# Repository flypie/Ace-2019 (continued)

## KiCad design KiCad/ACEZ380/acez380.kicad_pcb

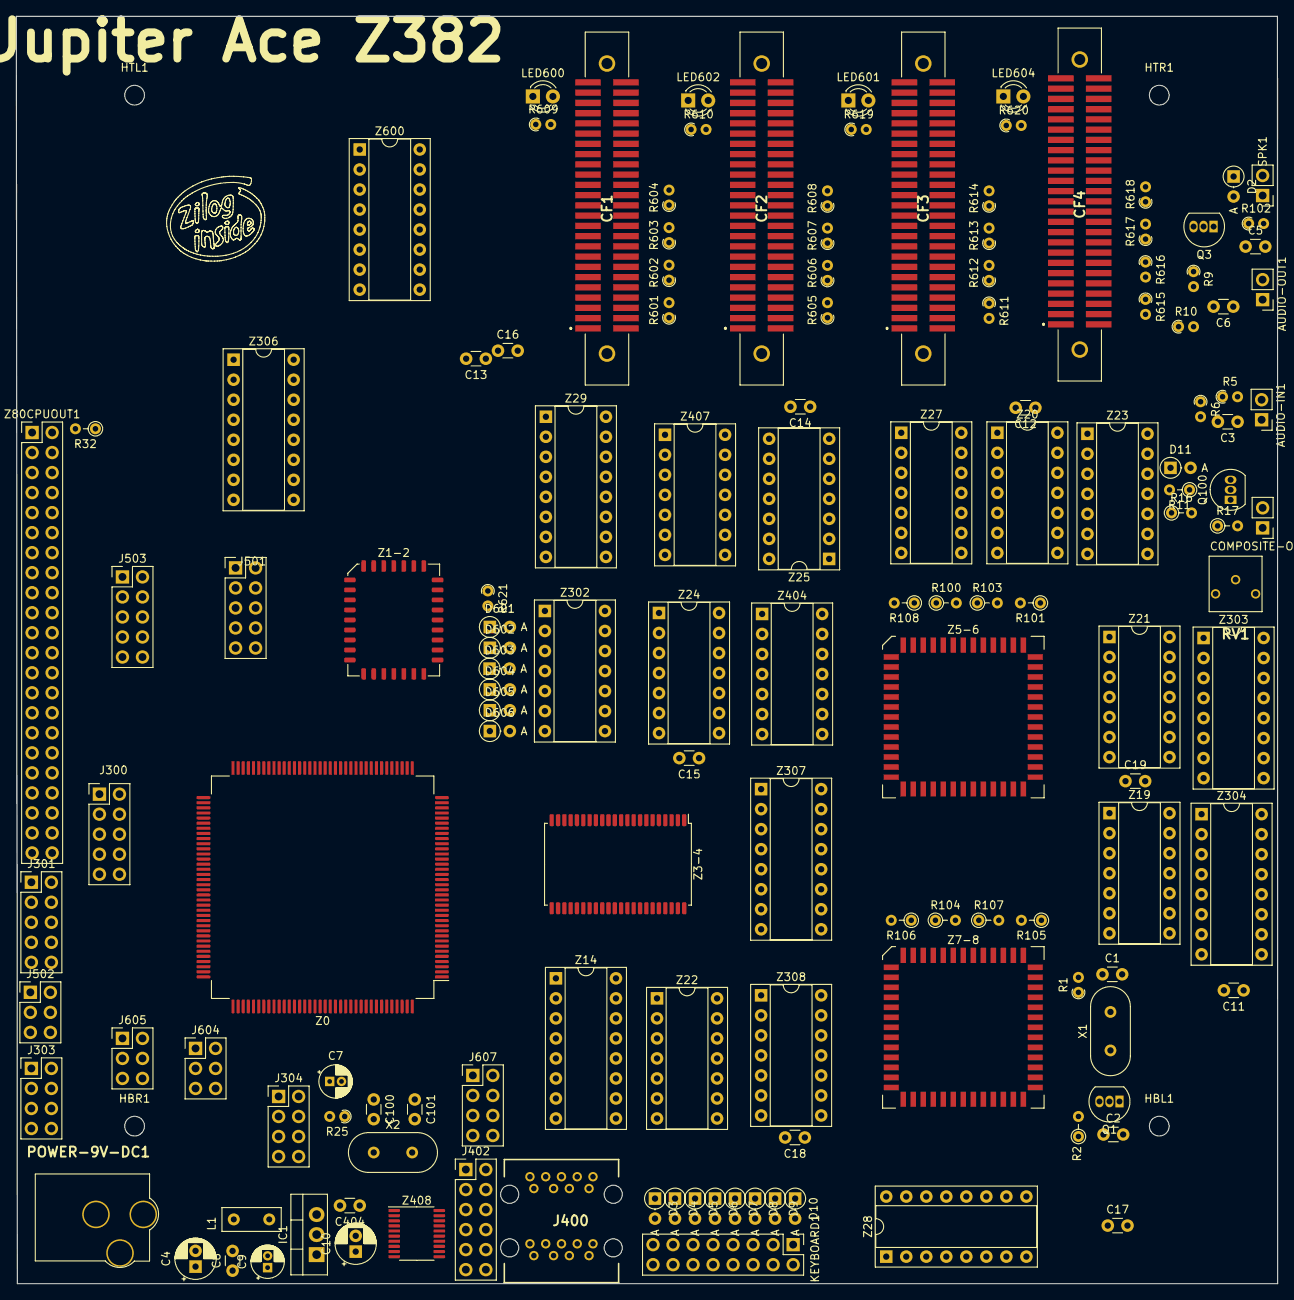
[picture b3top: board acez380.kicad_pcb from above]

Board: 2 copper layers, 160.0 x 160.8 mm, 146 parts (0 on the bottom side), 266 nets, no tracks yet.

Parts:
AUDIO-IN1: 332-02; PinHeader_1x02_P2.54mm_Vertical
AUDIO-OUT1: 332-02; PinHeader_1x02_P2.54mm_Vertical
C1: 30p; C_Disc_D3.0mm_W1.6mm_P2.50mm
C2: 100p; C_Disc_D3.0mm_W1.6mm_P2.50mm
C3, C6: 47nF; C_Disc_D3.0mm_W1.6mm_P2.50mm
C4, C10: 100uf; CP_Radial_D5.0mm_P2.00mm
C5: 47pF; C_Disc_D3.0mm_W1.6mm_P2.50mm
C7: 1U; CP_Radial_D4.0mm_P1.50mm
C8, C11, C12, C13, C14, C15, C16, C17, C18, C19: 100nf; C_Disc_D3.0mm_W1.6mm_P2.50mm
C9: 100uf; CP_Radial_D4.0mm_P1.50mm
C100, C101: 22p; C_Disc_D3.0mm_W1.6mm_P2.50mm
C404: 1u; C_Disc_D3.0mm_W1.6mm_P2.50mm
CF1, CF2, CF3, CF4: 5788643-1; 57886431
COMPOSITE-OUT1: COMPOSITE-OUT1; PinHeader_1x02_P2.54mm_Vertical
D2, D3, D4, D5, D6, D7, D8, D9, D10, D11, D601, D602, D603, D604, D605, D606: 1N4148; D_DO-35_SOD27_P2.54mm_Vertical_AnodeUp
HBL1: MountingHole; MountingHole_2.5mm
HBR1: MountingHole; MountingHole_2.5mm
HTL1: MountingHole; MountingHole_2.5mm
HTR1: MountingHole; MountingHole_2.5mm
IC1: LM7805_TO220; TO-220-3_Vertical
J300, J301, J501, J503: Conn_02x05_Odd_Even; PinHeader_2x05_P2.54mm_Vertical
J303, J304, J607: Conn_02x04_Odd_Even; PinHeader_2x04_P2.54mm_Vertical
J400: 48409-0003
J402: Conn_02x06_Odd_Even; PinHeader_2x06_P2.54mm_Vertical
J502, J604, J605: Conn_02x03_Odd_Even; PinHeader_2x03_P2.54mm_Vertical
KEYBOARD1: Conn_02x08_Odd_Even; PinHeader_2x08_P2.54mm_Vertical
L1: 100 nH; KEMET_SBT_0260T
LED600, LED601, LED602, LED604: WP3A8HD; LED_D3.0mm
Logo1: ZilogBack; ZilogInsideBack
Logo2: ZilogFront; ZilogInsideFront
POWER-9V-DC1: Conn_01x02; 163179PHEX
Q1, Q100: 2N3904; TO-92_Inline
Q3: BC183; TO-92L_Inline
R1: 4k7; R_Axial_DIN0204_L3.6mm_D1.6mm_P1.90mm_Vertical
R2: 47k; R_Axial_DIN0204_L3.6mm_D1.6mm_P2.54mm_Vertical
R5, R601, R602, R603, R604, R605, R606, R607, R608, R611, R612, R613, R614, R615, R616, R617, R618: 1K; R_Axial_DIN0204_L3.6mm_D1.6mm_P1.90mm_Vertical
R6: 12k; R_Axial_DIN0204_L3.6mm_D1.6mm_P1.90mm_Vertical
R9: 22k; R_Axial_DIN0204_L3.6mm_D1.6mm_P1.90mm_Vertical
R10: 10k; R_Axial_DIN0204_L3.6mm_D1.6mm_P1.90mm_Vertical
R11, R16: 1K5; R_Axial_DIN0204_L3.6mm_D1.6mm_P2.54mm_Vertical
R17: 100; R_Axial_DIN0204_L3.6mm_D1.6mm_P2.54mm_Vertical
R25: 220k; R_Axial_DIN0204_L3.6mm_D1.6mm_P1.90mm_Vertical
R32: 1K0; R_Axial_DIN0204_L3.6mm_D1.6mm_P2.54mm_Vertical
R100, R101, R103, R104, R105, R106, R107, R108: 270; R_Axial_DIN0204_L3.6mm_D1.6mm_P2.54mm_Vertical
R102: 200; R_Axial_DIN0204_L3.6mm_D1.6mm_P1.90mm_Vertical
R609, R610, R619, R620: 500; R_Axial_DIN0204_L3.6mm_D1.6mm_P1.90mm_Vertical
R621: 10; R_Axial_DIN0204_L3.6mm_D1.6mm_P1.90mm_Vertical
RV1: 100; 3362H1103LF
SPK1: SPk1; PinHeader_1x02_P2.54mm_Vertical
X1: CRYSTALHC49U-V 6.556MHz; Crystal_HC49-U_Vertical
X2: 20MHz; Crystal_HC49-U_Vertical
Z0: Z80-182-L182-VQFP-100; PQFP-144_28x28mm_P0.65mm
Z1-2: SST39SF010-LCC; PLCC-32_11.4x14.0mm_P1.27mm
Z3-4: CY62158; TSOP-II-44_10.16x18.41mm_P0.8mm
Z5-6: IDT71321-421-52PIN-PLCC; PLCC-52
Z7-8: IDT71321; PLCC-52
Z14: SN74LS367AN; DIP-16_W7.62mm_Socket
Z19: 74AHCT00; DIP-14_W7.62mm_Socket
Z20: 74AHCT08; DIP-14_W7.62mm_Socket
Z21, Z22: 74AHCT11; DIP-14_W7.62mm_Socket
Z23: 74AHCT86; DIP-14_W7.62mm_Socket
Z24: SN74AHCT02N; DIP-14_W7.62mm_Socket
Z25: 74AHCT02; DIP-14_W7.62mm_Socket
Z27: SN74AHCT74N; DIP-14_W7.62mm_Socket
Z28: 74AHCT166; DIP-16_W7.62mm_Socket
Z29: SN74AHCT138N; DIP-16_W7.62mm_Socket
Z80CPUOUT1: Conn_02x22_Odd_Even; PinHeader_2x22_P2.54mm_Vertical
Z302: 74AHCT32; DIP-14_W7.62mm_Socket
Z303, Z304: CD74HCT4040E; DIP-16_W7.62mm_Socket
Z306: SN74AHCT04N; DIP-16_W7.62mm_Socket
Z307, Z600: SN74AHCT139N; DIP-16_W7.62mm_Socket
Z308: SN74AHCT04N; DIP-14_W7.62mm_Socket
Z404: 74LS21; DIP-14_W7.62mm_Socket
Z407: 74AHCT30D; DIP-14_W7.62mm_Socket
Z408: STM8S003F3P; TSSOP-20_4.4x6.5mm_P0.65mm

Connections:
50Hz: Z21.6, Z25.6, Z306.9
+5V: C10.1, C11.1, C12.1, C13.1, C14.1, C15.1, C16.1, C17.1, C18.1, C19.1, CF1.13 (Vcc), CF1.38 (Vcc), CF2.13 (Vcc), CF2.38 (Vcc), CF3.13 (Vcc), CF3.38 (Vcc), CF4.13 (Vcc), CF4.38 (Vcc), D2.1 (K), IC1.3 (VO), J300.9, J301.9, J303.7, J304.7, J400.1, J400.10, J402.11, J501.9, J502.5, J503.9, J604.5, J605.5, J607.7, Q100.3 (C), R1.1, R16.2, R25.1, R100.1, R101.1, R103.1, R104.1, R105.1, R106.1, R107.1, R108.1, R601.1, R602.1, R603.1, R604.1, R605.1, R606.1, R607.1, R608.1, R609.1, R610.1, R611.1, R612.1, R613.1, R614.1, R615.1, R616.1, R617.1, R618.1, R619.1, R620.1, SPK1.2, Z0.5 (VDD_1), Z0.23 (VDD_2), Z0.41 (VDD_3), Z0.59 (VDD_4), Z0.77 (VDD_5), Z0.86 (VSS_6), Z0.95 (VDD_6), Z0.113 (VDD_7), Z0.131 (VDD_8), Z1-2.32 (VCC), Z3-4.11 (VCC1), Z3-4.33 (VCC2), Z3-4.40 (CE2), Z5-6.51 (~CER), Z5-6.52 (VCC), Z7-8.51 (~CER), Z7-8.52 (VCC), Z14.16 (VCC), Z19.14 (VCC), Z20.14 (VCC), Z21.14 (VCC), Z22.14 (VCC), Z23.14 (VCC), Z24.14 (VCC), Z25.14 (VCC), Z27.1 (~R), Z27.4 (~S), Z27.10 (~S), Z27.13 (~R), Z27.14 (VCC), Z28.9 (Clr), Z28.16 (VCC), Z29.16 (VCC), Z80CPUOUT1.37, Z302.14 (VCC), Z303.16 (VDD), Z304.16 (VDD), Z306.14 (VCC), Z307.16 (VCC), Z308.14 (VCC), Z404.14 (VCC), Z407.14 (VCC), Z408.9 (VDD), Z600.16 (VCC)
+9V: C4.1, C8.1, L1.1, POWER-9V-DC1.A
+9Vsm: C9.1, IC1.1 (VI), L1.2, Z80CPUOUT1.39
/ADDRDECODE/~3C00-3FFF: Z302.6, Z407.11, Z407.12
/ADDRDECODE/~CPUFONT: Z302.9, Z302.12, Z307.5 (O1)
/VDG/INVERTCHAR: Z5-6.34 (I/O7R), Z20.13
/VDG/SH~LD: Z5-6.46 (~OER), Z5-6.50 (R~WR), Z7-8.46 (~OER), Z7-8.50 (R~WR), Z19.6, Z28.15 (PE)
/VDG/VIDEN: Z19.4, Z20.9, Z22.6
/VDG/VIDEO: D11.2 (A), Q100.2 (B), R11.1, R16.1
/~BUSAK: Z0.132 (~BUSACK), Z80CPUOUT1.28
/~BUSRQ: Z0.133 (~BUSREQ), Z80CPUOUT1.24
/~HALT: Z0.121 (~HALT), Z80CPUOUT1.38
/~WAIT: Z0.130 (~WAIT), Z80CPUOUT1.26
/~WE: R32.2, Z80CPUOUT1.1
A0: Z0.22 (A0), Z1-2.12 (A0), Z3-4.5 (A0), Z5-6.7 (A0L), Z7-8.7 (A0L), Z80CPUOUT1.7, Z307.14 (A0)
A1: Z0.21 (A1), Z1-2.11 (A1), Z3-4.4 (A1), Z5-6.8 (A1L), Z7-8.8 (A1L), Z80CPUOUT1.8, Z307.13 (A1)
A2: Z0.20 (A2), Z1-2.10 (A2), Z3-4.3 (A2), Z5-6.9 (A2L), Z7-8.9 (A2L), Z80CPUOUT1.17, Z308.3
A3: Z0.19 (A3), Z1-2.9 (A3), Z3-4.2 (A3), Z5-6.10 (A3L), Z7-8.10 (A3L), Z80CPUOUT1.10, Z308.4
A4: Z0.18 (A4), Z1-2.8 (A4), Z3-4.1 (A4), Z5-6.11 (A4L), Z7-8.11 (A4L), Z80CPUOUT1.12, Z308.5
A5: Z0.17 (A5), Z1-2.7 (A5), Z3-4.44 (A5), Z5-6.12 (A5L), Z7-8.12 (A5L), Z80CPUOUT1.14, Z308.6
A6: Z0.16 (A6), Z1-2.6 (A6), Z3-4.43 (A6), Z5-6.13 (A6L), Z7-8.13 (A6L), Z80CPUOUT1.16, Z308.11
A7: Z0.15 (A7), Z1-2.5 (A7), Z3-4.42 (A7), Z5-6.14 (A7L), Z7-8.14 (A7L), Z80CPUOUT1.9, Z308.12
A8: D10.1 (K), Z0.13 (A8), Z1-2.27 (A8), Z3-4.39 (A8), Z5-6.15 (A8L), Z7-8.15 (A8L), Z80CPUOUT1.11, Z600.3 (A1)
A9: D9.1 (K), Z0.12 (A9), Z1-2.26 (A9), Z3-4.28 (A9), Z5-6.16 (A9L), Z7-8.16 (A9L), Z80CPUOUT1.13, Z600.2 (A0)
A10: CF1.18 (A2), CF2.18 (A2), CF3.18 (A2), CF4.18 (A2), D8.1 (K), Z0.11 (A10), Z1-2.23 (A10), Z3-4.27 (A10), Z80CPUOUT1.15, Z302.2, Z306.11
A11: CF1.19 (A1), CF2.19 (A1), CF3.19 (A1), CF4.19 (A1), D7.1 (K), Z0.10 (A11), Z1-2.25 (A11), Z3-4.26 (A11), Z80CPUOUT1.33, Z307.2 (A0)
A12: CF1.20 (A0), CF2.20 (A0), CF3.20 (A0), CF4.20 (A0), D6.1 (K), Z0.9 (A12), Z1-2.4 (A12), Z3-4.25 (A12), Z80CPUOUT1.31, Z307.3 (A1)
A13: D5.1 (K), Z0.8 (A13), Z1-2.28 (A13), Z3-4.24 (A13), Z29.1 (A0), Z80CPUOUT1.29
A14: D4.1 (K), D606.2 (A), Z0.7 (A14), Z1-2.29 (A14), Z3-4.23 (A14), Z29.2 (A1), Z80CPUOUT1.27
A15: D3.1 (K), D605.2 (A), Z0.6 (A15), Z1-2.2 (A16), Z3-4.22 (A15), Z29.3 (A2), Z80CPUOUT1.25
A16: D604.2 (A), Z0.4 (A16), Z1-2.3 (A15), Z3-4.21 (A16)
A17: D603.2 (A), Z0.3 (A17), Z3-4.20 (A17)
A18: D602.2 (A), Z0.2 (A18), Z3-4.19 (A18)
A19: D601.2 (A), Z0.1 (A19), Z3-4.18 (A19)
A20: J607.1, Z0.144 (A20)
A21: J607.3, Z0.143 (A21)
A22: J607.4, Z0.142 (A22)
A23: J607.2, Z0.141 (A23)
CKA0: J303.6, Z0.53 (PB5/CKA0), Z0.92 (CKA0/HDRQ1/PCRESET)
CKA1: J304.6, Z0.49 (PC3/CKA1), Z0.65 (CKA1/HA10)
CKS: J502.3, Z0.64 (CKS/HA11)
CNT0: Z22.5, Z303.9 (Q0)
CNT1: Z22.4, Z303.7 (Q1)
CNT2: Z22.3, Z303.6 (Q2)
DA0: CF1.21 (D0), CF2.21 (D0), CF3.21 (D0), CF4.21 (D0), Z0.40 (D0), Z1-2.13 (D0), Z3-4.9 (I/O0), Z5-6.17 (I/O0L), Z7-8.17 (I/O0L), Z14.3 (O1a), Z27.2 (D), Z80CPUOUT1.6
DA1: CF1.22 (D1), CF2.22 (D1), CF3.22 (D1), CF4.22 (D1), Z0.39 (D1), Z1-2.14 (D1), Z3-4.10 (I/O1), Z5-6.18 (I/O1L), Z7-8.18 (I/O1L), Z14.5 (O2a), Z80CPUOUT1.5
DA2: CF1.23 (D2), CF2.23 (D2), CF3.23 (D2), CF4.23 (D2), Z0.38 (D2), Z1-2.15 (D2), Z3-4.13 (I/O2), Z5-6.19 (I/O2L), Z7-8.19 (I/O2L), Z14.7 (O3a), Z80CPUOUT1.4
DA3: CF1.2 (D3), CF2.2 (D3), CF3.2 (D3), CF4.2 (D3), Z0.37 (D3), Z1-2.17 (D3), Z3-4.14 (I/O3), Z5-6.20 (I/O3L), Z7-8.20 (I/O3L), Z14.9 (O4a), Z80CPUOUT1.21
DA4: CF1.3 (D4), CF2.3 (D4), CF3.3 (D4), CF4.3 (D4), Z0.36 (D4), Z1-2.18 (D4), Z3-4.32 (I/O5), Z5-6.21 (I/O4L), Z7-8.21 (I/O4L), Z14.11 (O5b), Z80CPUOUT1.23
DA5: CF1.4 (D5), CF2.4 (D5), CF3.4 (D5), CF4.4 (D5), Z0.35 (D5), Z1-2.19 (D5), Z3-4.31 (I/O4), Z5-6.22 (I/O5L), Z7-8.22 (I/O5L), Z14.13 (O6b), Z80CPUOUT1.19
DA6: CF1.5 (D6), CF2.5 (D6), CF3.5 (D6), CF4.5 (D6), Z0.34 (D6), Z1-2.20 (D6), Z3-4.35 (I/O6), Z5-6.23 (I/O6L), Z7-8.23 (I/O6L), Z80CPUOUT1.3
DA7: CF1.6 (D7), CF2.6 (D7), CF3.6 (D7), CF4.6 (D7), Z0.33 (D7), Z1-2.21 (D7), Z3-4.36 (I/O7), Z5-6.24 (I/O7L), Z7-8.24 (I/O7L), Z80CPUOUT1.2
ENDOFSCR: Z20.2, Z25.2, Z304.12 (Q8)
EOL: Z21.11, Z22.13, Z25.3, Z303.12 (Q8), Z304.10 (CLK)
FONTCHAR0: Z7-8.45 (A0R), Z304.9 (Q0)
FONTCHAR1: Z7-8.44 (A1R), Z304.7 (Q1)
FONTCHAR2: Z7-8.43 (A2R), Z304.6 (Q2)
GND: AUDIO-IN1.2, AUDIO-OUT1.1, C2.2, C4.2, C7.2, C8.2, C9.2, C10.2, C11.2, C12.2, C13.2, C14.2, C15.2, C16.2, C17.2, C18.2, C19.2, C100.1, C101.1, C404.2, CF1.1 (GND), CF1.8 (A10), CF1.9 (~ATASEL), CF1.10 (A9), CF1.11 (A8), CF1.12 (A7), CF1.14 (A6), CF1.15 (A5), CF1.16 (A4), CF1.17 (A3), CF1.39 (~CSEL), CF1.50 (GND), CF2.1 (GND), CF2.8 (A10), CF2.9 (~ATASEL), CF2.10 (A9), CF2.11 (A8), CF2.12 (A7), CF2.14 (A6), CF2.15 (A5), CF2.16 (A4), CF2.17 (A3), CF2.39 (~CSEL), CF2.50 (GND), CF3.1 (GND), CF3.8 (A10), CF3.9 (~ATASEL), CF3.10 (A9), CF3.11 (A8), CF3.12 (A7), CF3.14 (A6), CF3.15 (A5), CF3.16 (A4), CF3.17 (A3), CF3.39 (~CSEL), CF3.50 (GND), CF4.1 (GND), CF4.8 (A10), CF4.9 (~ATASEL), CF4.10 (A9), CF4.11 (A8), CF4.12 (A7), CF4.14 (A6), CF4.15 (A5), CF4.16 (A4), CF4.17 (A3), CF4.39 (~CSEL), CF4.50 (GND), COMPOSITE-OUT1.2, IC1.2 (GND), J300.10, J301.10, J303.8, J304.8, J400.4, J400.5, J400.6, J400.7, J400.8, J400.9, J400.13, J400.14, J400.15, J400.16, J400.17, J400.18, J402.12, J501.10, J502.6, J503.10, J604.6, J605.6, J607.8, POWER-9V-DC1.C, Q1.1 (E), Q3.3 (E), R5.1, R6.1, R17.2, R621.2, Z0.14 (VSS_1), Z0.32 (VSS_2), Z0.68 (VSS_3), Z0.104 (VSS_7), Z0.117 (~MSIZE), Z0.122 (VSS_5), Z0.140 (VSS_8), Z1-2.16 (GND), Z3-4.12 (VSS1), Z3-4.34 (VSS2), Z5-6.5 (A10L), Z5-6.26 (GND), Z5-6.47 (A10R), Z7-8.5 (A10L), Z7-8.26 (GND), Z7-8.47 (A10R), Z14.8 (GND), Z19.7 (GND), Z20.7 (GND), Z21.7 (GND), Z22.7 (GND), Z23.7 (GND), Z24.7 (GND), Z25.7 (GND), Z27.7 (GND), Z28.6 (CE), Z28.8 (GND), Z28.14 (H), Z29.8 (GND), Z80CPUOUT1.41, Z80CPUOUT1.43, Z80CPUOUT1.44, Z302.7 (GND), Z303.8 (VSS), Z304.8 (VSS), Z306.7 (GND), Z307.8 (GND), Z308.7 (GND), Z404.7 (GND), Z407.7 (GND), Z408.7 (VSS), Z600.8 (GND)
unnamed: AUDIO-IN1.1, C3.1, R5.2
unnamed: AUDIO-OUT1.2, C5.1, C6.1
unnamed: C1.1, Q1.3 (C), R1.2, R2.2, Z306.13
unnamed: C1.2, X1.2
unnamed: C2.1, Q1.2 (B), R2.1, X1.1
unnamed: C3.2, R6.2, Z14.14 (I6)
unnamed: C5.2, D2.2 (A), Q3.1 (C), R102.1
unnamed: C6.2, R10.2
unnamed: C100.2, X2.1, Z0.129 (CLKO)
unnamed: C101.2, X2.2, Z0.128 (CLKI)
unnamed: C404.1, Z408.8 (VCAP)
unnamed: CF1.7 (~CS0), Z600.4 (O0)
unnamed: CF1.32 (~CS1), R601.2
unnamed: CF1.36 (~WE), R602.2
unnamed: CF1.44 (~DMACK), R603.2
unnamed: CF1.45 (~DASP), LED600.1 (K)
unnamed: CF1.46 (~PDIAG), R604.2
unnamed: CF2.7 (~CS0), Z600.5 (O1)
unnamed: CF2.32 (~CS1), R605.2
unnamed: CF2.36 (~WE), R606.2
unnamed: CF2.44 (~DMACK), R607.2
unnamed: CF2.45 (~DASP), LED602.1 (K)
unnamed: CF2.46 (~PDIAG), R608.2
unnamed: CF3.7 (~CS0), Z600.6 (O2)
unnamed: CF3.32 (~CS1), R611.2
unnamed: CF3.36 (~WE), R612.2
unnamed: CF3.44 (~DMACK), R613.2
unnamed: CF3.45 (~DASP), LED601.1 (K)
unnamed: CF3.46 (~PDIAG), R614.2
unnamed: CF4.7 (~CS0), Z600.7 (O3)
unnamed: CF4.32 (~CS1), R615.2
unnamed: CF4.36 (~WE), R616.2
unnamed: CF4.44 (~DMACK), R617.2
unnamed: CF4.45 (~DASP), LED604.1 (K)
unnamed: CF4.46 (~PDIAG), R618.2
unnamed: COMPOSITE-OUT1.1, RV1.2
unnamed: D3.2 (A), KEYBOARD1.15
unnamed: D4.2 (A), KEYBOARD1.13
unnamed: D5.2 (A), KEYBOARD1.11
unnamed: D6.2 (A), KEYBOARD1.9
unnamed: D7.2 (A), KEYBOARD1.7
unnamed: D8.2 (A), KEYBOARD1.5
unnamed: D9.2 (A), KEYBOARD1.3
unnamed: D10.2 (A), KEYBOARD1.1
unnamed: D11.1 (K), Z25.4
unnamed: D601.1 (K), D602.1 (K), D603.1 (K), D604.1 (K), D605.1 (K), D606.1 (K), R621.1, Z306.1
unnamed: J400.2, Z408.6 (PA2)
unnamed: J400.3, Z408.5 (PA1)
unnamed: J400.11, Z408.12 (PB4)
unnamed: J400.12, Z408.11 (PB5)
unnamed: J402.1, Z408.17 (PC7)
unnamed: J402.2, Z408.3 (PD6)
unnamed: J402.3, Z408.16 (PC6)
unnamed: J402.4, Z408.2 (PD5)
unnamed: J402.5, Z408.15 (PC5)
unnamed: J402.6, Z408.1 (PD4)
unnamed: J402.7, Z408.10 (PA3)
unnamed: J402.8, Z408.20 (PD3)
unnamed: J402.9, Z408.18 (PD1)
unnamed: J402.10, Z408.19 (PD2)
unnamed: KEYBOARD1.2, Z14.2 (I1)
unnamed: KEYBOARD1.4, Z14.4 (I2)
unnamed: KEYBOARD1.6, Z14.6 (I3)
unnamed: KEYBOARD1.8, Z14.10 (I4)
unnamed: KEYBOARD1.10, Z14.12 (I5)
unnamed: LED600.2 (A), R609.2
unnamed: LED601.2 (A), R619.2
unnamed: LED602.2 (A), R610.2
unnamed: LED604.2 (A), R620.2
unnamed: Q3.2 (B), R9.1
unnamed: Q100.1 (E), R17.1, RV1.1
unnamed: R9.2, Z24.9, Z24.13
unnamed: R10.1, Z27.5 (Q)
unnamed: R11.2, Z23.11
unnamed: R100.2, Z5-6.4 (~INTL)
unnamed: R101.2, Z5-6.48 (~INTR)
unnamed: R102.2, SPK1.1
unnamed: R103.2, Z5-6.49 (~BUSYR)
unnamed: R104.2, Z7-8.4 (~INTL)
unnamed: R105.2, Z7-8.48 (~INTR)
unnamed: R106.2, Z7-8.3 (~BUSYL)
unnamed: R107.2, Z7-8.49 (~BUSYR)
unnamed: R108.2, Z5-6.3 (~BUSYL)
unnamed: Z5-6.27 (I/O0R), Z7-8.42 (A3R)
unnamed: Z5-6.28 (I/O1R), Z7-8.41 (A4R)
unnamed: Z5-6.29 (I/O2R), Z7-8.40 (A5R)
unnamed: Z5-6.30 (I/O3R), Z7-8.39 (A6R)
unnamed: Z5-6.31 (I/O4R), Z7-8.38 (A7R)
unnamed: Z5-6.32 (I/O5R), Z7-8.37 (A8R)
unnamed: Z5-6.33 (I/O6R), Z7-8.36 (A9R)
unnamed: Z14.1 (OEa), Z14.15 (OEb), Z306.6
unnamed: Z19.3, Z20.4
unnamed: Z19.5, Z20.6, Z20.12
unnamed: Z20.1, Z21.5, Z21.12
unnamed: Z20.3, Z304.11 (Reset)
unnamed: Z20.5, Z25.1
unnamed: Z20.8, Z27.11 (C)
unnamed: Z20.11, Z27.12 (D)
unnamed: Z21.8, Z303.11 (Reset)
unnamed: Z22.2, Z25.13
unnamed: Z22.12, Z25.5
unnamed: Z23.12, Z27.9 (Q)
unnamed: Z23.13, Z28.13 (Qh)
unnamed: Z24.1, Z24.8, Z27.3 (C)
unnamed: Z24.10, Z24.11
unnamed: Z24.4, Z24.12, Z306.5
unnamed: Z7-8.27 (I/O0R), Z28.1 (Ds)
unnamed: Z7-8.28 (I/O1R), Z28.2 (A)
unnamed: Z7-8.29 (I/O2R), Z28.3 (B)
unnamed: Z7-8.30 (I/O3R), Z28.4 (C)
unnamed: Z7-8.31 (I/O4R), Z28.5 (D)
unnamed: Z7-8.32 (I/O5R), Z28.10 (E)
unnamed: Z7-8.33 (I/O6R), Z28.11 (F)
unnamed: Z7-8.34 (I/O7R), Z28.12 (G)
unnamed: Z29.6 (E3), Z306.2
unnamed: Z29.7 (O7), Z407.6
unnamed: Z29.9 (O6), Z407.5
unnamed: Z29.10 (O5), Z407.4
unnamed: Z29.11 (O4), Z407.3
unnamed: Z29.12 (O3), Z407.2
unnamed: Z29.13 (O2), Z407.1
unnamed: Z29.14 (O1), Z307.1 (E)
unnamed: Z302.5, Z306.10
unnamed: Z306.4, Z308.1, Z308.2
unnamed: Z307.15 (E), Z308.8
PA0: J300.1, Z0.85 (PA0/HD0)
PA1: J300.3, Z0.84 (PA1/HD1)
PA2: J300.5, Z0.83 (PA2/HD2)
PA3: J300.7, Z0.82 (PA3/HD3)
PA4: J300.8, Z0.81 (PA4/HD4)
PA5: J300.6, Z0.80 (PA5/HD5)
PA6: J300.4, Z0.79 (PA6/HD6)
PA7: J300.2, Z0.78 (PA7/HD7)
PB0: J301.1, Z0.58 (PB0/CKS)
PB1: J301.3, Z0.57 (PB1/RXS)
PB2: J301.5, Z0.56 (PB2/TXS)
PC2: J501.5, Z0.109 (PC2/~TXEN2/TOUT)
PC4: J501.8, Z0.48 (PC4/IEO)
PC5: J501.6, Z0.47 (PC5/IEI)
PC6: J501.4, Z0.45 (PC6/~IOCS1)
PC7: J501.2, Z0.44 (PC7/~RAMCSH)
PD0: J503.1, Z0.76 (PD0/HA0)
PD1: J503.3, Z0.75 (PD1/HA1)
PD2: J503.5, Z0.74 (PD2/HA2)
PD3: J503.7, Z0.73 (PD3/HA3)
PD4: J503.8, Z0.72 (PD4/HA4)
PD5: J503.6, Z0.71 (PD5/HA5)
PD6: J503.4, Z0.70 (PD6/HA6)
PD7: J503.2, Z0.69 (PD7/HA7)
RxA0: J303.2, Z0.52 (PB6/RXA0), Z0.90 (RXA0/HDAK1/POOE)
RxA1: J304.2, Z0.55 (PB3/RXA1)
RxC0: J604.3, Z0.97 (RXC0/BLC0/PC0)
RxC1: J605.3, Z0.101 (RXC1/BLC1/PC1)
RxD0: J604.1, Z0.99 (RXD0/RXA0)
RxD1: J605.1, Z0.67 (RXA1/HA8), Z0.103 (RXD1/RXA1)
RxD2: Z0.108 (FSC/RXD2), Z408.13 (PC3)
RxS\~CTS: J502.2, Z0.63 (RXS/HAEN/~PCREG)
SCREENX0: Z5-6.45 (A0R), Z303.5 (Q3)
SCREENX1: Z5-6.44 (A1R), Z303.3 (Q4)
SCREENX2: Z5-6.43 (A2R), Z21.9, Z25.11, Z303.2 (Q5)
SCREENX3: Z5-6.42 (A3R), Z22.1, Z303.4 (Q6)
SCREENX4: Z5-6.41 (A4R), Z21.10, Z25.12, Z303.13 (Q7)
SCREENY0: Z5-6.40 (A5R), Z21.1, Z304.5 (Q3)
SCREENY1: Z5-6.39 (A6R), Z21.2, Z304.3 (Q4)
SCREENY2: Z5-6.38 (A7R), Z21.13, Z304.2 (Q5)
SCREENY3: Z5-6.37 (A8R), Z19.2, Z21.3, Z304.4 (Q6)
SCREENY4: Z5-6.36 (A9R), Z19.1, Z21.4, Z304.13 (Q7)
TxA0: J303.1, Z0.51 (PB7/TXA0), Z0.91 (TXA0/~HADRQ/~POOE1)
TxA1: J304.1, Z0.54 (PB4/TXA1), Z0.87 (TXA1/HINT1/PCIRQ)
TxC0: J604.4, Z0.96 (TXC0/FSC0/CKA0)
TxC1: J605.4, Z0.100 (TXC1/FCS1/CKA1)
TxD0: J604.2, Z0.98 (TXD0/TXA0)
TxD1: J605.2, Z0.102 (TXD1/TXA1)
TxD2: Z0.107 (DD/TXD2), Z408.14 (PC4)
TxS: J502.1, Z0.62 (TXS/~HDOEN/~INPACK)
~0000-1FFF: Z29.15 (O0), Z404.1
~3000-37FF: Z307.6 (O2), Z404.4
~3800-3BFF: Z302.3, Z404.5
~3800-3FFF: Z302.1, Z302.4, Z307.7 (O3)
~CFCS: Z307.9 (O3), Z600.1 (E)
~CPUCLK: Z0.127 (BUSCLK), Z80CPUOUT1.35
~CPUFONTRAM: Z7-8.1 (~CEL), Z302.11
~CPUFONTROM: Z302.8, Z404.2
~CPUVIDEORAM: Z5-6.1 (~CEL), Z307.4 (O0)
~CTS0: J303.4, Z0.61 (~CTS0/HRD/PCIORD), Z0.111 (~CTS0/~TREFA)
~CTS1: J304.4, Z0.60 (~CTS1/NWR/PCIOWR), Z0.110 (~CTS1/~TREFC)
~DCD0: J303.5, Z0.89 (DCD0/HDAK0/POWE), Z0.112 (~DCD0/~FTREFR)
~DCD1: J304.5, Z0.66 (DCD1/HA9)
~INT0: Z0.136 (~INT0), Z80CPUOUT1.42
~INT3: Z0.139 (~INT3), Z306.8
~IORD: Z0.125 (~IORD), Z24.6
~IOREQ: Z0.115 (~IORQ), Z80CPUOUT1.34, Z306.3
~IOWR: Z0.123 (~IOWR), Z24.3
~M1: Z0.116 (~M1), Z80CPUOUT1.20
~MRD: Z0.126 (~MRD), Z3-4.41 (~OE)
~MREQ: Z0.43 (~RAMCSL), Z29.4 (E1), Z29.5 (E2), Z80CPUOUT1.36
~MWR: Z0.124 (~MWR), Z3-4.17 (~WE)
~NMI: Z0.135 (~NMI), Z80CPUOUT1.40
~RAMSEL: R32.1, Z3-4.6 (~CE1), Z407.8
~RD: CF1.34 (~IORD), CF2.34 (~IORD), CF3.34 (~IORD), CF4.34 (~IORD), Z5-6.6 (~OEL), Z7-8.6 (~OEL), Z80CPUOUT1.32, Z302.10
~RESET: C7.1, CF1.41 (~RESET), CF2.41 (~RESET), CF3.41 (~RESET), CF4.41 (~RESET), R25.2, Z0.134 (~RESET), Z80CPUOUT1.22, Z408.4 (NRST)
~ROMSEL: Z1-2.22 (CE), Z1-2.24 (OE), Z404.6
~RTS0: J303.3, Z0.93 (~TXEN0/~RTS0)
~RTS1: J304.3, Z0.94 (~TXEN/~RTS1)
~TAPECS: Z24.2, Z24.5, Z307.10 (O2)
~VIDEOCLK: Z20.10, Z28.7 (Clk), Z303.10 (CLK), Z306.12
~WR: CF1.35 (~IOWR), CF2.35 (~IOWR), CF3.35 (~IOWR), CF4.35 (~IOWR), Z5-6.2 (R~WL), Z7-8.2 (R~WL), Z80CPUOUT1.30, Z302.13

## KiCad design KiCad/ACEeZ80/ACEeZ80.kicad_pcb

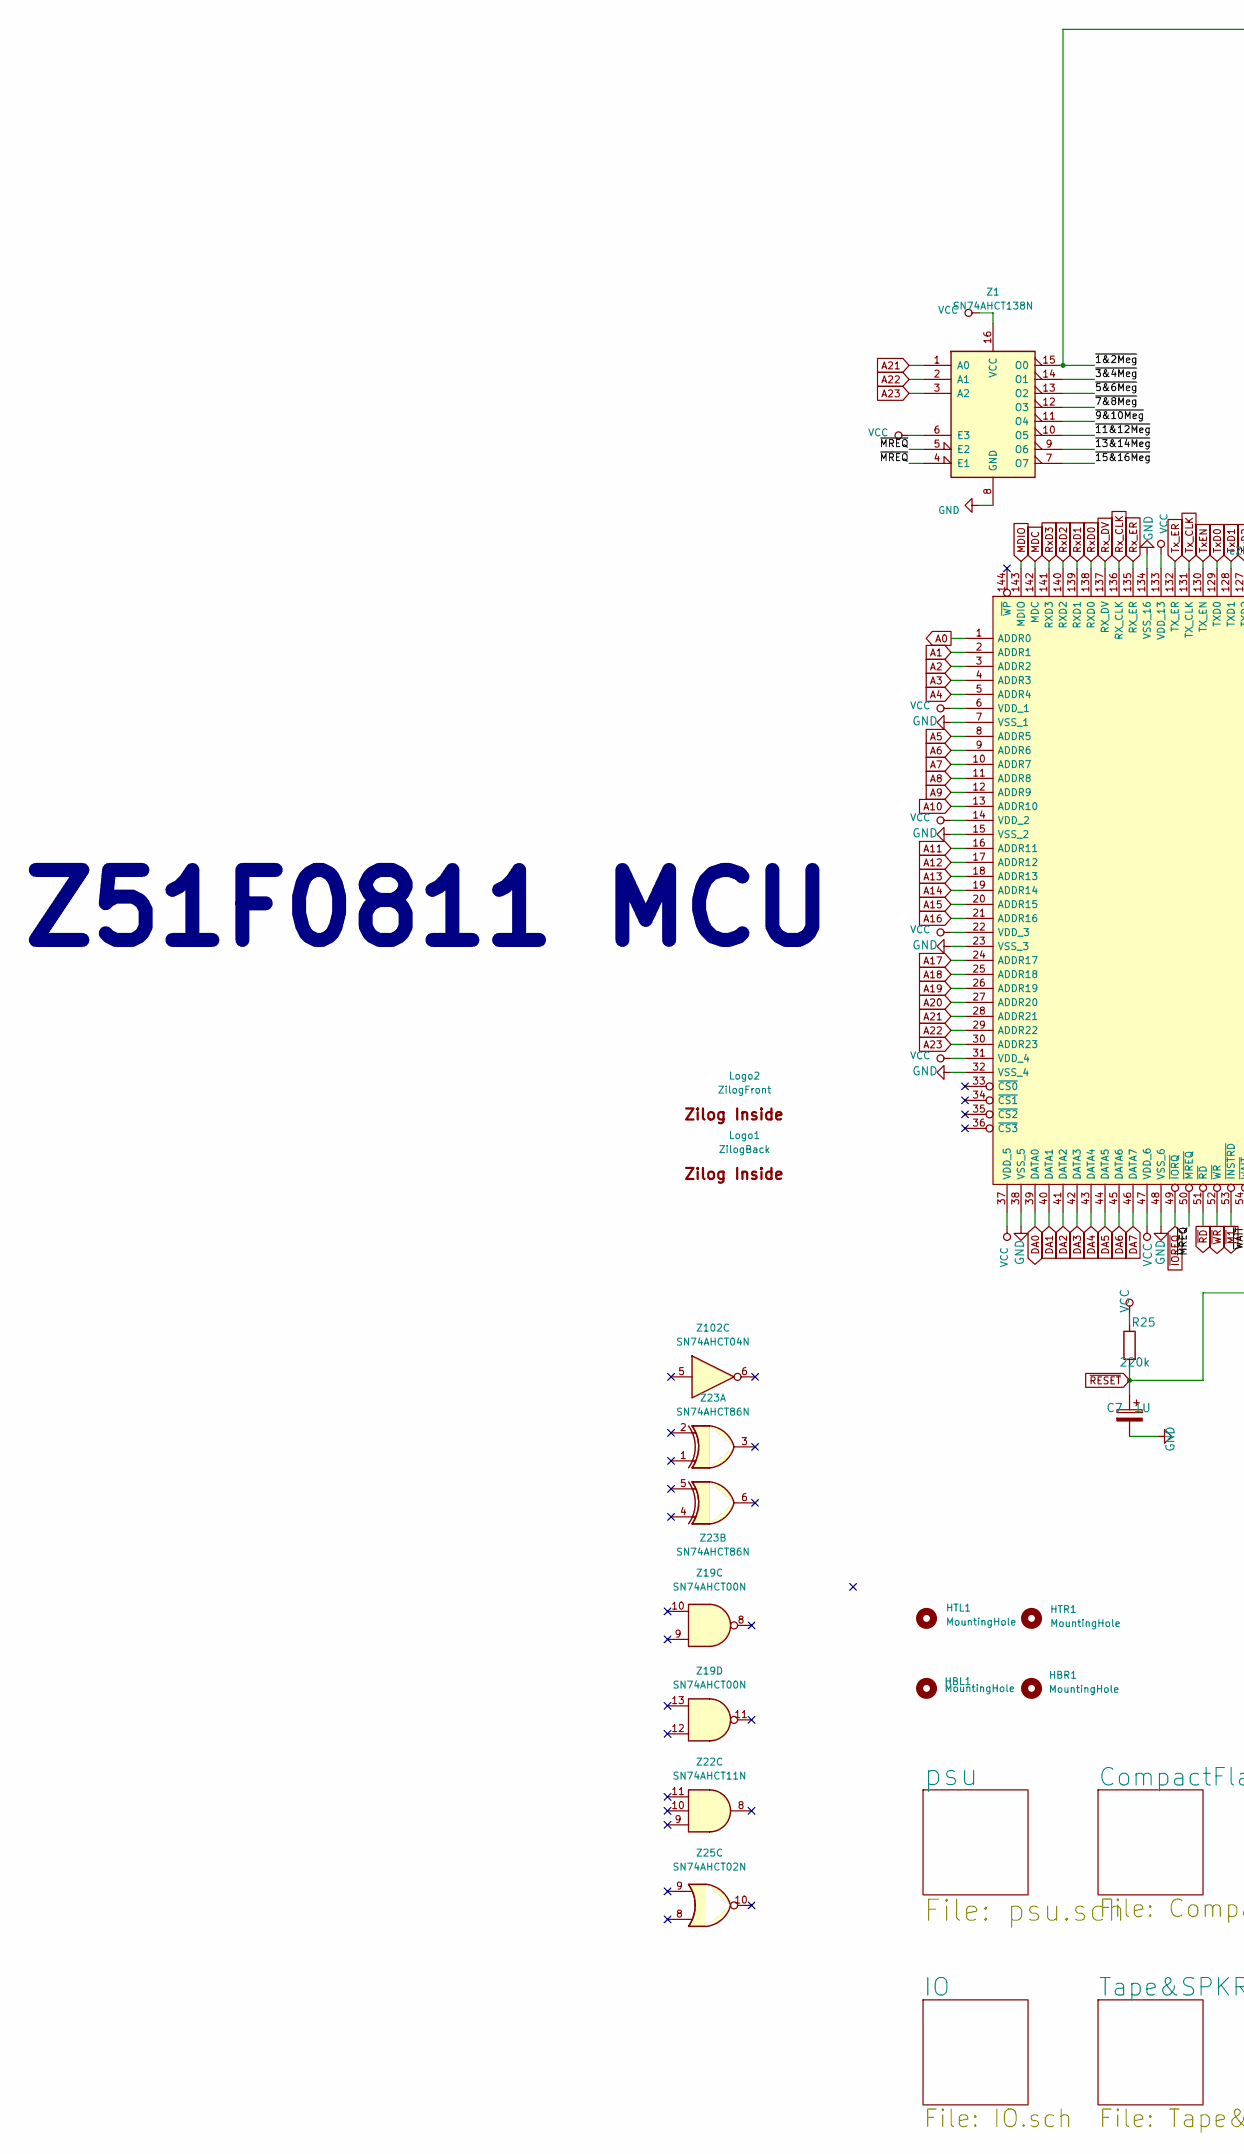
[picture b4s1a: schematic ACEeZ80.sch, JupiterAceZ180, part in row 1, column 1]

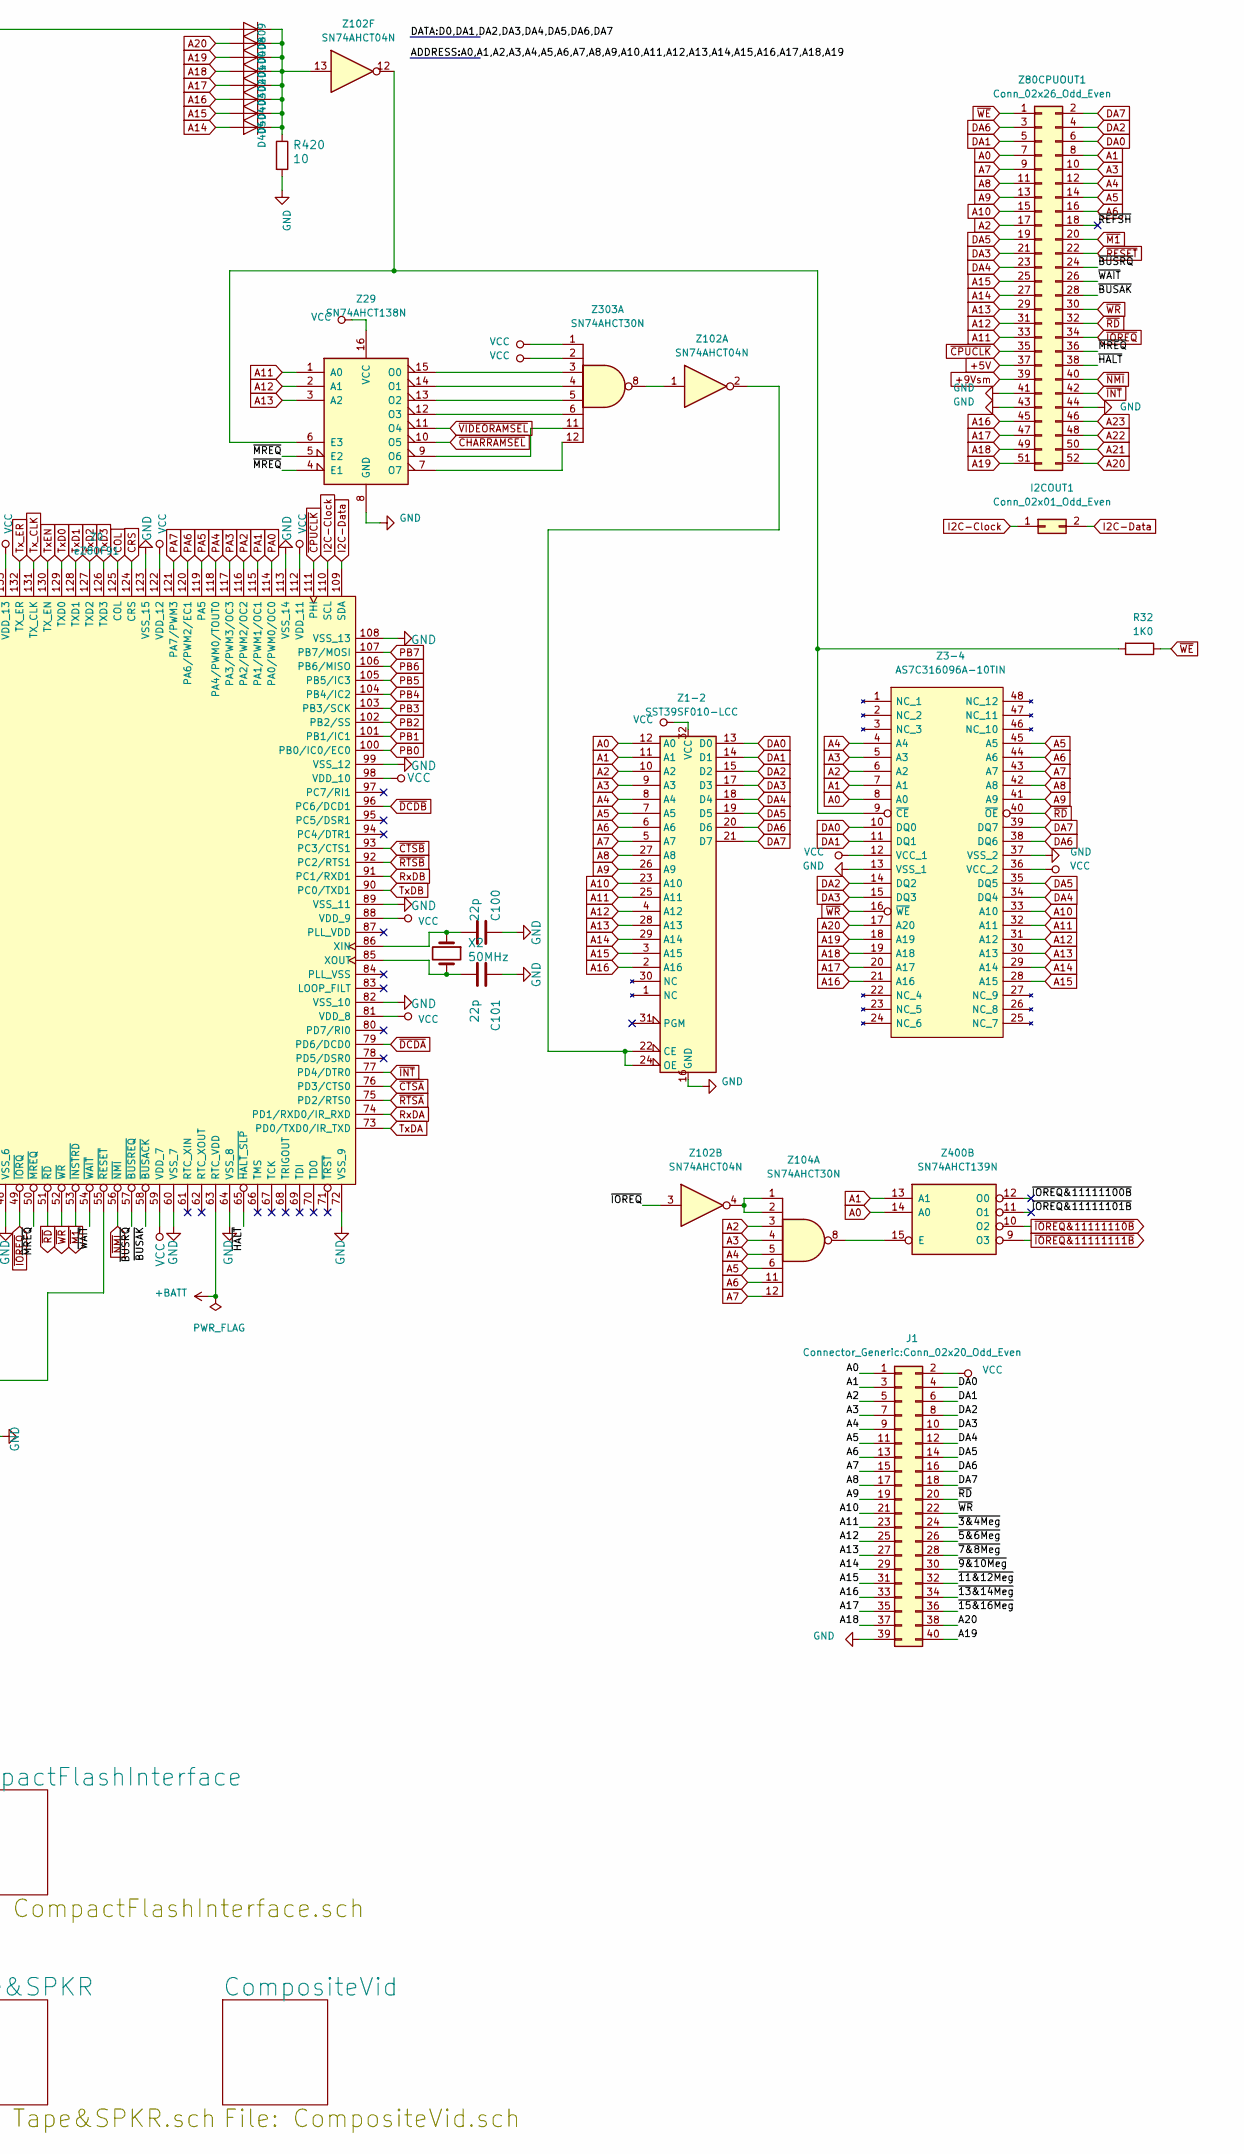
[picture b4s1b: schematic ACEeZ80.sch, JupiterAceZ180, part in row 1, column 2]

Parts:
C7: 1U; CP_Radial_D4.0mm_P1.50mm
C100, C101: 22p; C_Disc_D5.0mm_W2.5mm_P5.00mm
D400, D401, D402, D403, D404, D405, D408, D409: 1N4148; D_DO-35_SOD27_P2.54mm_Vertical_AnodeUp
HBL1: MountingHole; MountingHole_2.5mm
HBR1: MountingHole; MountingHole_2.5mm
HTL1: MountingHole; MountingHole_2.5mm
HTR1: MountingHole; MountingHole_2.5mm
I2COUT1: Conn_02x01_Odd_Even; PinHeader_2x01_P2.54mm_Vertical
J1: Connector_Generic:Conn_02x20_Odd_Even; PinSocket_2x20_P1.27mm_Vertical
Logo1: ZilogBack; ZilogInsideBack
Logo2: ZilogFront; ZilogInsideFront
R25: 220k; R_Axial_DIN0204_L3.6mm_D1.6mm_P1.90mm_Vertical
R32: 1K0; R_Axial_DIN0204_L3.6mm_D1.6mm_P2.54mm_Vertical
R420: 10; R_Axial_DIN0204_L3.6mm_D1.6mm_P1.90mm_Vertical
X2: 50MHz; Crystal_HC49-U_Vertical
Z0: eZ80F91; LQFP-144_20x20mm_P0.5mm; Manufacturer_Part_Number EZ80L92AZ050EG
Z1, Z29: SN74AHCT138N; DIP-16_W7.62mm
Z1-2: SST39SF010-LCC; PLCC-32_THT_Socket_11.4x14.0mm_P1.27mm; Mouser Part Number 556-AT28C25615PU
Z3-4: AS7C316096A-10TIN; TSOP-I-48_18.4x12mm_P0.5mm; Manufacturer_Part_Number AS7C316096A-10TIN
Z19: SN74AHCT00N; DIP-14_W7.62mm
Z22: SN74AHCT11N; DIP-14_W7.62mm
Z23: SN74AHCT86N; DIP-14_W7.62mm
Z25: SN74AHCT02N; DIP-14_W7.62mm
Z80CPUOUT1: Conn_02x26_Odd_Even; PinHeader_2x26_P2.54mm_Vertical
Z102: SN74AHCT04N; DIP-14_W7.62mm
Z104, Z303: SN74AHCT30N; SOIC-14_3.9x8.7mm_P1.27mm
Z400: SN74AHCT139N; DIP-16_W7.62mm

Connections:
+9Vsm: Z80CPUOUT1.39; also elsewhere on the board
+BATT: Z0.63 (RTC_VDD)
/~1&2Meg: D409.2 (A), Z1.15 (O0)
/~3&4Meg: J1.24, Z1.14 (O1)
/~5&6Meg: J1.26, Z1.13 (O2)
/~7&8Meg: J1.28, Z1.12 (O3)
/~9&10Meg: J1.30, Z1.11 (O4)
/~11&12Meg: J1.32, Z1.10 (O5)
/~13&14Meg: J1.34, Z1.9 (O6)
/~15&16Meg: J1.36, Z1.7 (O7)
/~BUSAK: Z0.58 (~BUSACK), Z80CPUOUT1.28
/~BUSRQ: Z0.57 (~BUSREQ), Z80CPUOUT1.24
/~HALT: Z0.65 (~HALT_SLP), Z80CPUOUT1.38
/~IOREQ&11111100B: Z400.12 (O0)
/~IOREQ&11111101B: Z400.11 (O1)
/~MREQ: Z0.50 (~MREQ), Z1.4 (E1), Z1.5 (E2), Z29.4 (E1), Z29.5 (E2), Z80CPUOUT1.36
/~REFSH: Z80CPUOUT1.18
/~WAIT: Z0.54 (~WAIT), Z80CPUOUT1.26
A0: J1.1, Z0.1 (ADDR0), Z1-2.12 (A0), Z3-4.8 (A0), Z80CPUOUT1.7, Z400.14 (A0); also elsewhere on the board
A1: J1.3, Z0.2 (ADDR1), Z1-2.11 (A1), Z3-4.7 (A1), Z80CPUOUT1.8, Z400.13 (A1); also elsewhere on the board
A2: J1.5, Z0.3 (ADDR2), Z1-2.10 (A2), Z3-4.6 (A2), Z80CPUOUT1.17, Z104.3; also elsewhere on the board
A3: J1.7, Z0.4 (ADDR3), Z1-2.9 (A3), Z3-4.5 (A3), Z80CPUOUT1.10, Z104.4; also elsewhere on the board
A4: J1.9, Z0.5 (ADDR4), Z1-2.8 (A4), Z3-4.4 (A4), Z80CPUOUT1.12, Z104.5; also elsewhere on the board
A5: J1.11, Z0.8 (ADDR5), Z1-2.7 (A5), Z3-4.45 (A5), Z80CPUOUT1.14, Z104.6; also elsewhere on the board
A6: J1.13, Z0.9 (ADDR6), Z1-2.6 (A6), Z3-4.44 (A6), Z80CPUOUT1.16, Z104.11; also elsewhere on the board
A7: J1.15, Z0.10 (ADDR7), Z1-2.5 (A7), Z3-4.43 (A7), Z80CPUOUT1.9, Z104.12; also elsewhere on the board
A8: J1.17, Z0.11 (ADDR8), Z1-2.27 (A8), Z3-4.42 (A8), Z80CPUOUT1.11; also elsewhere on the board
A9: J1.19, Z0.12 (ADDR9), Z1-2.26 (A9), Z3-4.41 (A9), Z80CPUOUT1.13; also elsewhere on the board
A10: J1.21, Z0.13 (ADDR10), Z1-2.23 (A10), Z3-4.33 (A10), Z80CPUOUT1.15; also elsewhere on the board
A11: J1.23, Z0.16 (ADDR11), Z1-2.25 (A11), Z3-4.32 (A11), Z29.1 (A0), Z80CPUOUT1.33; also elsewhere on the board
A12: J1.25, Z0.17 (ADDR12), Z1-2.4 (A12), Z3-4.31 (A12), Z29.2 (A1), Z80CPUOUT1.31; also elsewhere on the board
A13: J1.27, Z0.18 (ADDR13), Z1-2.28 (A13), Z3-4.30 (A13), Z29.3 (A2), Z80CPUOUT1.29; also elsewhere on the board
A14: D405.2 (A), J1.29, Z0.19 (ADDR14), Z1-2.29 (A14), Z3-4.29 (A14), Z80CPUOUT1.27; also elsewhere on the board
A15: D404.2 (A), J1.31, Z0.20 (ADDR15), Z1-2.3 (A15), Z3-4.28 (A15), Z80CPUOUT1.25; also elsewhere on the board
A16: D403.2 (A), J1.33, Z0.21 (ADDR16), Z1-2.2 (A16), Z3-4.21 (A16), Z80CPUOUT1.45
A17: D402.2 (A), J1.35, Z0.24 (ADDR17), Z3-4.20 (A17), Z80CPUOUT1.47
A18: D401.2 (A), J1.37, Z0.25 (ADDR18), Z3-4.19 (A18), Z80CPUOUT1.49
A19: D400.2 (A), J1.40, Z0.26 (ADDR19), Z3-4.18 (A19), Z80CPUOUT1.51
A20: D408.2 (A), J1.38, Z0.27 (ADDR20), Z3-4.17 (A20), Z80CPUOUT1.52
A21: Z0.28 (ADDR21), Z1.1 (A0), Z80CPUOUT1.50
A22: Z0.29 (ADDR22), Z1.2 (A1), Z80CPUOUT1.48
A23: Z0.30 (ADDR23), Z1.3 (A2), Z80CPUOUT1.46
COL: Z0.125 (COL); also elsewhere on the board
CRS: Z0.124 (CRS); also elsewhere on the board
DA0: J1.4, Z0.39 (DATA0), Z1-2.13 (D0), Z3-4.10 (DQ0), Z80CPUOUT1.6; also elsewhere on the board
DA1: J1.6, Z0.40 (DATA1), Z1-2.14 (D1), Z3-4.11 (DQ1), Z80CPUOUT1.5; also elsewhere on the board
DA2: J1.8, Z0.41 (DATA2), Z1-2.15 (D2), Z3-4.14 (DQ2), Z80CPUOUT1.4; also elsewhere on the board
DA3: J1.10, Z0.42 (DATA3), Z1-2.17 (D3), Z3-4.15 (DQ3), Z80CPUOUT1.21; also elsewhere on the board
DA4: J1.12, Z0.43 (DATA4), Z1-2.18 (D4), Z3-4.34 (DQ4), Z80CPUOUT1.23; also elsewhere on the board
DA5: J1.14, Z0.44 (DATA5), Z1-2.19 (D5), Z3-4.35 (DQ5), Z80CPUOUT1.19; also elsewhere on the board
DA6: J1.16, Z0.45 (DATA6), Z1-2.20 (D6), Z3-4.38 (DQ6), Z80CPUOUT1.3; also elsewhere on the board
DA7: J1.18, Z0.46 (DATA7), Z1-2.21 (D7), Z3-4.39 (DQ7), Z80CPUOUT1.2; also elsewhere on the board
I2C-Clock: I2COUT1.1, Z0.110 (SCL); also elsewhere on the board
I2C-Data: I2COUT1.2, Z0.109 (SDA); also elsewhere on the board
MDC: Z0.142 (MDC); also elsewhere on the board
MDIO: Z0.143 (MDIO); also elsewhere on the board
unnamed: C100.2, X2.1, Z0.86 (XIN)
unnamed: C101.2, X2.2, Z0.85 (XOUT)
unnamed: D400.1 (K), D401.1 (K), D402.1 (K), D403.1 (K), D404.1 (K), D405.1 (K), D408.1 (K), D409.1 (K), R420.1, Z102.13
unnamed: R32.2, Z3-4.9 (~CE), Z29.6 (E3), Z102.12
unnamed: Z1-2.22 (CE), Z1-2.24 (OE), Z102.2
unnamed: Z29.7 (O7), Z303.12
unnamed: Z29.9 (O6), Z303.11
unnamed: Z29.12 (O3), Z303.6
unnamed: Z29.13 (O2), Z303.5
unnamed: Z29.14 (O1), Z303.4
unnamed: Z29.15 (O0), Z303.3
unnamed: Z102.1, Z303.8
unnamed: Z102.4, Z104.1, Z104.2
unnamed: Z104.8, Z400.15 (E)
PA0: Z0.114 (PA0/PWM0/OC0); also elsewhere on the board
PA1: Z0.115 (PA1/PWM1/OC1); also elsewhere on the board
PA2: Z0.116 (PA2/PWM2/OC2); also elsewhere on the board
PA3: Z0.117 (PA3/PWM3/OC3); also elsewhere on the board
PA4: Z0.118 (PA4/PWM0/TOUT0); also elsewhere on the board
PA5: Z0.119 (PA5); also elsewhere on the board
PA6: Z0.120 (PA6/PWM2/EC1); also elsewhere on the board
PA7: Z0.121 (PA7/PWM3); also elsewhere on the board
PB0: Z0.100 (PB0/IC0/EC0); also elsewhere on the board
PB1: Z0.101 (PB1/IC1); also elsewhere on the board
PB2: Z0.102 (PB2/SS); also elsewhere on the board
PB3: Z0.103 (PB3/SCK); also elsewhere on the board
PB4: Z0.104 (PB4/IC2); also elsewhere on the board
PB5: Z0.105 (PB5/IC3); also elsewhere on the board
PB6: Z0.106 (PB6/MISO); also elsewhere on the board
PB7: Z0.107 (PB7/MOSI); also elsewhere on the board
RxD0: Z0.138 (RXD0); also elsewhere on the board
RxD1: Z0.139 (RXD1); also elsewhere on the board
RxD2: Z0.140 (RXD2); also elsewhere on the board
RxD3: Z0.141 (RXD3); also elsewhere on the board
RxDA: Z0.74 (PD1/RXD0/IR_RXD); also elsewhere on the board
RxDB: Z0.91 (PC1/RXD1); also elsewhere on the board
Rx_CLK: Z0.136 (RX_CLK); also elsewhere on the board
Rx_DV: Z0.137 (RX_DV); also elsewhere on the board
Rx_ER: Z0.135 (RX_ER); also elsewhere on the board
TxD0: Z0.129 (TXD0); also elsewhere on the board
TxD1: Z0.128 (TXD1); also elsewhere on the board
TxD2: Z0.127 (TXD2); also elsewhere on the board
TxD3: Z0.126 (TXD3); also elsewhere on the board
TxDA: Z0.73 (PD0/TXD0/IR_TXD); also elsewhere on the board
TxDB: Z0.90 (PC0/TXD1); also elsewhere on the board
TxEN: Z0.130 (TX_EN); also elsewhere on the board
Tx_CLK: Z0.131 (TX_CLK); also elsewhere on the board
Tx_ER: Z0.132 (TX_ER); also elsewhere on the board
~CHARRAMSEL: Z29.10 (O5); also elsewhere on the board
~CPUCLK: Z0.111 (PHI), Z80CPUOUT1.35
~CTSA: Z0.76 (PD3/CTS0); also elsewhere on the board
~CTSB: Z0.93 (PC3/CTS1); also elsewhere on the board
~DCDA: Z0.79 (PD6/DCD0); also elsewhere on the board
~DCDB: Z0.96 (PC6/DCD1); also elsewhere on the board
~INT: Z0.77 (PD4/DTR0), Z80CPUOUT1.42; also elsewhere on the board
~IOREQ: Z0.49 (~IORQ), Z80CPUOUT1.34, Z102.3
~IOREQ&11111110B: Z400.10 (O2); also elsewhere on the board
~IOREQ&11111111B: Z400.9 (O3); also elsewhere on the board
~M1: Z0.53 (~INSTRD), Z80CPUOUT1.20
~NMI: Z0.56 (~NMI), Z80CPUOUT1.40
~RD: J1.20, Z0.51 (~RD), Z3-4.40 (~OE), Z80CPUOUT1.32; also elsewhere on the board
~RESET: C7.1, R25.2, Z0.55 (~RESET), Z80CPUOUT1.22; also elsewhere on the board
~RTSA: Z0.75 (PD2/RTS0); also elsewhere on the board
~RTSB: Z0.92 (PC2/RTS1); also elsewhere on the board
~VIDEORAMSEL: Z29.11 (O4); also elsewhere on the board
~WE: R32.1, Z80CPUOUT1.1
~WR: J1.22, Z0.52 (~WR), Z3-4.16 (~WE), Z80CPUOUT1.30; also elsewhere on the board

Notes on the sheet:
Z51F0811 MCU
